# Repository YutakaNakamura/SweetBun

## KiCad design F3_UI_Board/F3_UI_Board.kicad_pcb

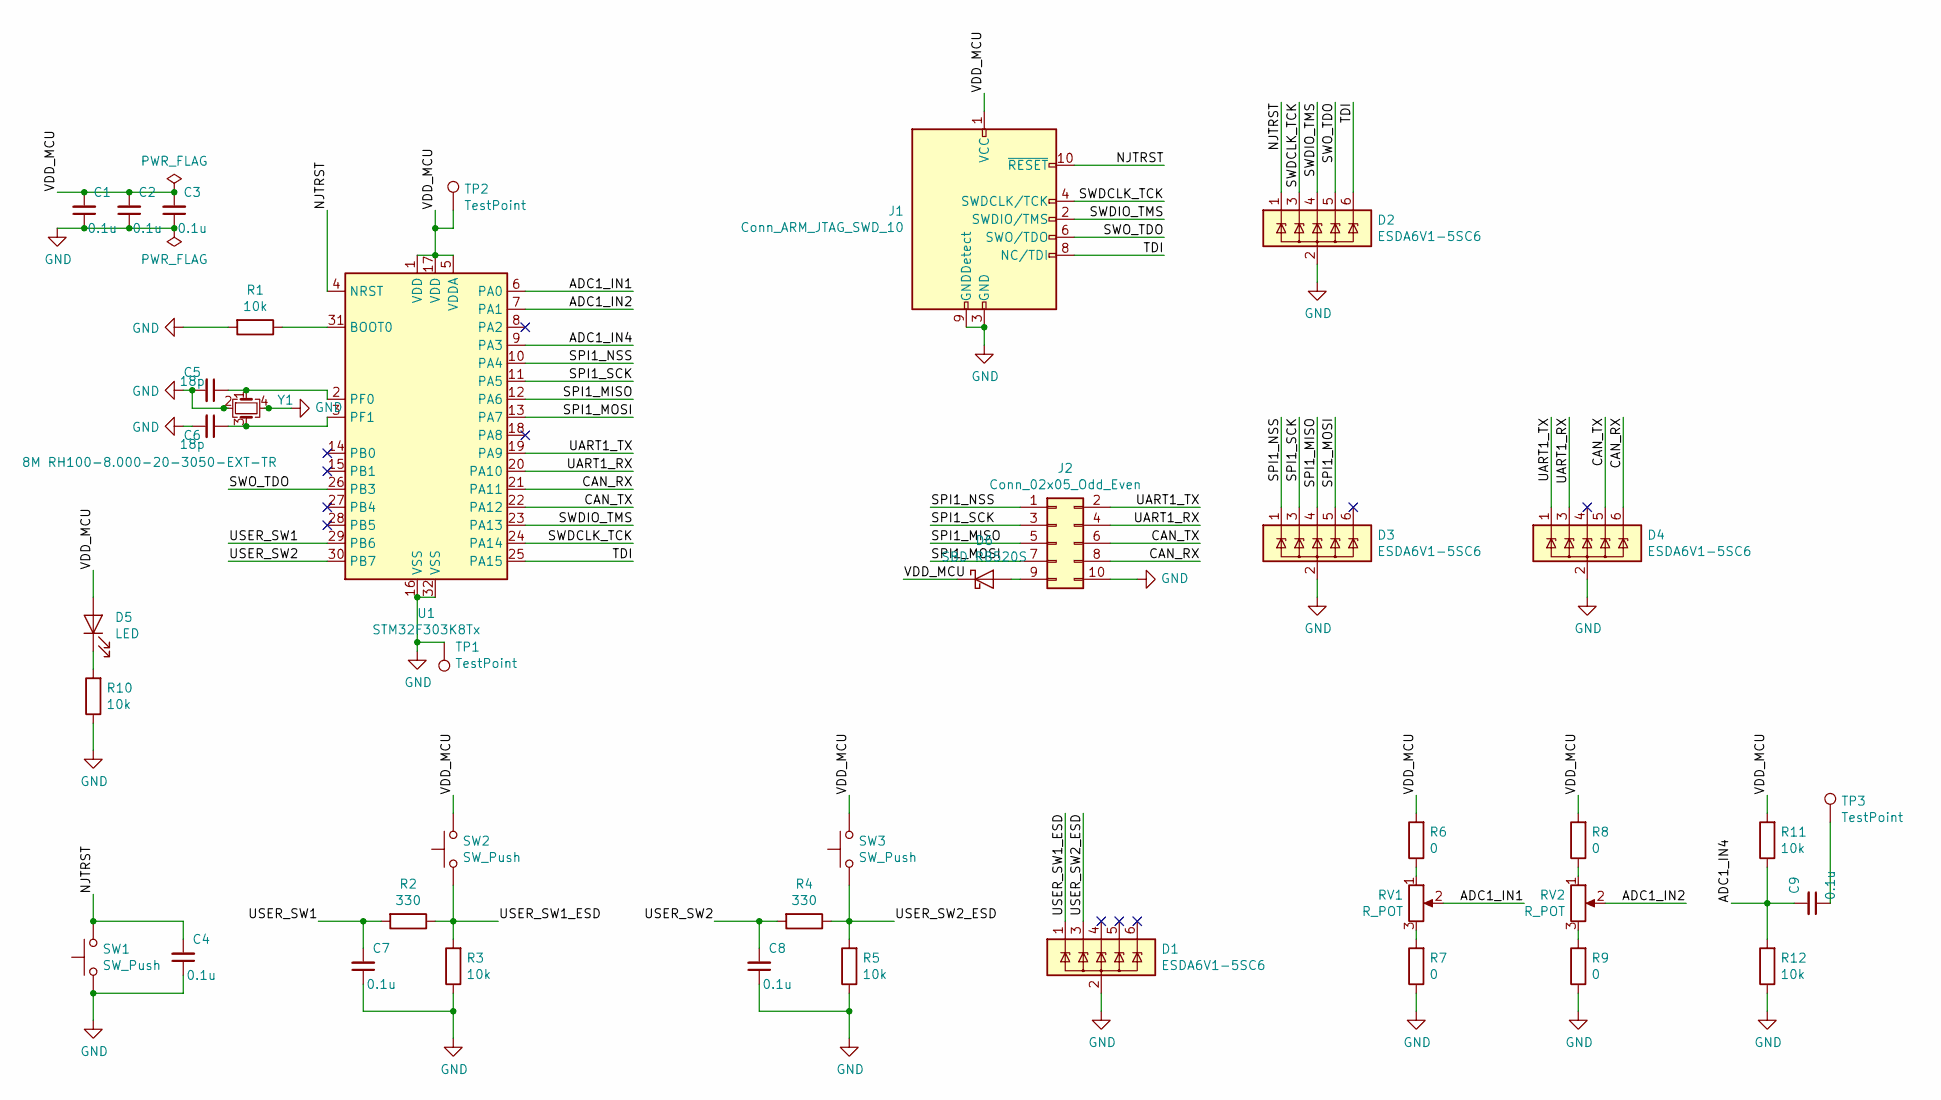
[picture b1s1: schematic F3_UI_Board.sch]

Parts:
C1, C2, C3, C4, C7, C8, C9: 0.1u; C_0603_1608Metric
C5, C6: 18p; C_0603_1608Metric
D1, D2, D3, D4: ESDA6V1-5SC6; SOT-23-6
D5: LED; LED_0603_1608Metric
D6: SBD RB520S; D_0603_1608Metric
J1: Conn_ARM_JTAG_SWD_10; PinHeader_2x05_P1.27mm_Vertical_SMD
J2: Conn_02x05_Odd_Even; PinHeader_2x05_P1.27mm_Vertical
R1, R3, R5, R10, R11, R12: 10k; R_0603_1608Metric
R2, R4: 330; R_0603_1608Metric
R6, R7, R8, R9: 0; R_0603_1608Metric
RV1, RV2: R_POT; Potentiometer_Bourns_3386F_Vertical
SW1, SW2, SW3: SW_Push; SW_SPST_PTS810
TP1, TP2, TP3: TestPoint; Pin_D1.0mm_L10.0mm
U1: STM32F303K8Tx; LQFP-32_7x7mm_P0.8mm
Y1: 8M RH100-8.000-20-3050-EXT-TR; Crystal_SMD_3225-4Pin_3.2x2.5mm

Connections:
/ADC1_IN1: RV1.2, U1.6 (PA0)
/ADC1_IN2: RV2.2, U1.7 (PA1)
/ADC1_IN4: C9.2, R11.1, R12.2, U1.9 (PA3)
/CAN_RX: D4.6 (IO5), J2.8, U1.21 (PA11)
/CAN_TX: D4.5 (IO4), J2.6, U1.22 (PA12)
/NJTRST: C4.2, D2.1 (IO1), J1.10 (~RESET~), SW1.2, U1.4 (NRST)
/SPI1_MISO: D3.4 (IO3), J2.5, U1.12 (PA6)
/SPI1_MOSI: D3.5 (IO4), J2.7, U1.13 (PA7)
/SPI1_NSS: D3.1 (IO1), J2.1, U1.10 (PA4)
/SPI1_SCK: D3.3 (IO2), J2.3, U1.11 (PA5)
/SWDCLK_TCK: D2.3 (IO2), J1.4 (SWDCLK/TCK), U1.24 (PA14)
/SWDIO_TMS: D2.4 (IO3), J1.2 (SWDIO/TMS), U1.23 (PA13)
/SWO_TDO: D2.5 (IO4), J1.6 (SWO/TDO), U1.26 (PB3)
/TDI: D2.6 (IO5), J1.8 (NC/TDI), U1.25 (PA15)
/UART1_RX: D4.3 (IO2), J2.4, U1.20 (PA10)
/UART1_TX: D4.1 (IO1), J2.2, U1.19 (PA9)
/USER_SW1: C7.2, R2.2, U1.29 (PB6)
/USER_SW1_ESD: D1.1 (IO1), R2.1, R3.2, SW2.1
/USER_SW2: C8.2, R4.2, U1.30 (PB7)
/USER_SW2_ESD: D1.3 (IO2), R4.1, R5.2, SW3.1
/VDD_MCU: C1.2, C2.2, C3.2, D5.2 (A), D6.1 (K), J1.1 (VCC), R6.2, R8.2, R11.2, SW2.2, SW3.2, TP2.1, U1.1 (VDD), U1.5 (VDDA), U1.17 (VDD)
GND: C1.1, C2.1, C3.1, C4.1, C5.2, C6.2, C7.1, C8.1, D1.2 (GND), D2.2 (GND), D3.2 (GND), D4.2 (GND), J1.3 (GND), J1.5 (GND), J1.9 (GNDDetect), J2.10, R1.2, R3.1, R5.1, R7.1, R9.1, R10.1, R12.1, SW1.1, TP1.1, U1.16 (VSS), U1.32 (VSS), Y1.2, Y1.4
unnamed: C5.1, U1.2 (PF0), Y1.1
unnamed: C6.1, U1.3 (PF1), Y1.3
unnamed: C9.1, TP3.1
unnamed: D5.1 (K), R10.2
unnamed: D6.2 (A), J2.9
unnamed: R1.1, U1.31 (BOOT0)
unnamed: R6.1, RV1.1
unnamed: R7.2, RV1.3
unnamed: R8.1, RV2.1
unnamed: R9.2, RV2.3

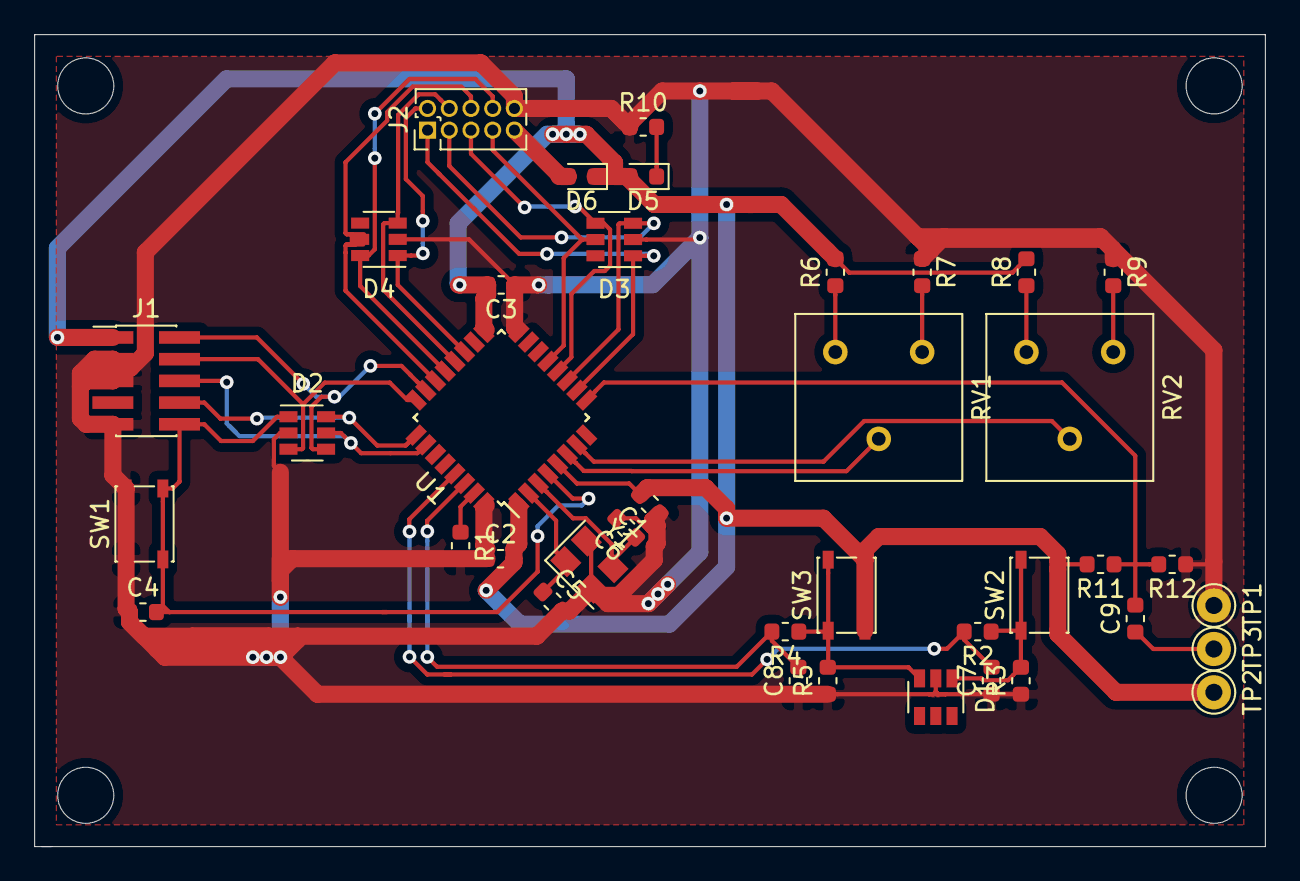
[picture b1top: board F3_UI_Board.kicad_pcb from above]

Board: 2 copper layers, 72.0 x 47.5 mm, 39 parts (0 on the bottom side), 32 nets.

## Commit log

2020-03-18 F3 UI
2020-03-18 [fix] pull up
2020-03-18 [add] dot
